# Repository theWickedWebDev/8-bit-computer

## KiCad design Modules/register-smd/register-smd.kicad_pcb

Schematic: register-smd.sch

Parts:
C1, C2, C3: C; C_0805_2012Metric; JLC C15525
C4: CP1; CP_Radial_D5.0mm_P2.50mm
D1, D2, D3, D4, D5, D6, D7, D8, D9, D10, D11, D12, D13, D14, D15, D16, D17, D18, D19, D20, D21, D22, D23, D24, D25, D26, D27, D28, D29, D30, D31, D32: LED; LED_0805_2012Metric
J1: Screw_Terminal_01x02; TerminalBlock_Phoenix_MKDS-1,5-2_1x02_P5.00mm_Horizontal
J2: Conn_01x16; PinHeader_1x16_P2.54mm_Horizontal
J8: Conn_01x18; PinHeader_1x18_P2.54mm_Horizontal
R1, R2, R3, R4, R5, R6, R7, R8, R9, R10, R11, R12, R13, R14, R15, R16, R17, R18, R19, R20, R21, R22, R23, R24, R25, R26, R27, R28, R29, R30, R31, R32, R33, R34, R35, R36, R37, R38: R_Small_US; R_0805_2012Metric; JLC C4109
U1, U3, U6: 74HC273; DIP-20_W7.62mm_Socket; JLCPCB Part # C9030
U2: 74HC08; DIP-14_W7.62mm_Socket
U4: 74LS04; DIP-14_W7.62mm_Socket
U5, U7, U47: 74HC245; DIP-20_W7.62mm_Socket

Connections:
!AI: J8.13, R32.2, U4.1
!AO: J8.14, R33.2, U4.3
!BI: J8.15, R34.2, U4.5
!BO: J8.16, R35.2, U4.9
!CI: J8.17, R36.2, U4.11
!CO: J8.18, R37.2, U4.13
/A0: D1.2 (A), J2.1, U1.2 (Q0), U47.2 (A0)
/A1: D2.2 (A), J2.2, U1.5 (Q1), U47.3 (A1)
/A2: D3.2 (A), J2.3, U1.6 (Q2), U47.4 (A2)
/A3: D4.2 (A), J2.4, U1.9 (Q3), U47.5 (A3)
/A4: D5.2 (A), J2.5, U1.12 (Q4), U47.6 (A4)
/A5: D6.2 (A), J2.6, U1.15 (Q5), U47.7 (A5)
/A6: D7.2 (A), J2.7, U1.16 (Q6), U47.8 (A6)
/A7: D8.2 (A), J2.8, U1.19 (Q7), U47.9 (A7)
/B0: D12.2 (A), J2.9, U3.2 (Q0), U5.2 (A0)
/B1: D13.2 (A), J2.10, U3.5 (Q1), U5.3 (A1)
/B2: D14.2 (A), J2.11, U3.6 (Q2), U5.4 (A2)
/B3: D15.2 (A), J2.12, U3.9 (Q3), U5.5 (A3)
/B4: D16.2 (A), J2.13, U3.12 (Q4), U5.6 (A4)
/B5: D17.2 (A), J2.14, U3.15 (Q5), U5.7 (A5)
/B6: D18.2 (A), J2.15, U3.16 (Q6), U5.8 (A6)
/B7: D19.2 (A), J2.16, U3.19 (Q7), U5.9 (A7)
/C0: D22.2 (A), U6.2 (Q0), U7.2 (A0)
/C1: D23.2 (A), U6.5 (Q1), U7.3 (A1)
/C2: D24.2 (A), U6.6 (Q2), U7.4 (A2)
/C3: D25.2 (A), U6.9 (Q3), U7.5 (A3)
/C4: D26.2 (A), U6.12 (Q4), U7.6 (A4)
/C5: D27.2 (A), U6.15 (Q5), U7.7 (A5)
/C6: D28.2 (A), U6.16 (Q6), U7.8 (A6)
/C7: D29.2 (A), U6.19 (Q7), U7.9 (A7)
AI: D9.2 (A), U2.1, U4.2
AO: D11.2 (A), U4.4, U47.19 (CE)
BI: D20.2 (A), U2.4, U4.6
BO: D21.2 (A), U4.8, U5.19 (CE)
BUS_00: J8.3, U1.3 (D0), U3.3 (D0), U5.18 (B0), U6.3 (D0), U7.18 (B0), U47.18 (B0)
BUS_01: J8.4, U1.4 (D1), U3.4 (D1), U5.17 (B1), U6.4 (D1), U7.17 (B1), U47.17 (B1)
BUS_02: J8.5, U1.7 (D2), U3.7 (D2), U5.16 (B2), U6.7 (D2), U7.16 (B2), U47.16 (B2)
BUS_03: J8.6, U1.8 (D3), U3.8 (D3), U5.15 (B3), U6.8 (D3), U7.15 (B3), U47.15 (B3)
BUS_04: J8.7, U1.13 (D4), U3.13 (D4), U5.14 (B4), U6.13 (D4), U7.14 (B4), U47.14 (B4)
BUS_05: J8.8, U1.14 (D5), U3.14 (D5), U5.13 (B5), U6.14 (D5), U7.13 (B5), U47.13 (B5)
BUS_06: J8.9, U1.17 (D6), U3.17 (D6), U5.12 (B6), U6.17 (D6), U7.12 (B6), U47.12 (B6)
BUS_07: J8.10, U1.18 (D7), U3.18 (D7), U5.11 (B7), U6.18 (D7), U7.11 (B7), U47.11 (B7)
CI: D30.2 (A), U2.9, U4.10
CLOCK: J8.11, U2.2, U2.5, U2.10
CO: D31.2 (A), U4.12, U7.19 (CE)
GND: C1.2, C2.2, C3.2, C4.2, J1.1, J8.2, R1.2, R2.2, R3.2, R4.2, R5.2, R6.2, R7.2, R8.2, R9.2, R10.2, R11.2, R12.2, R13.2, R14.2, R15.2, R16.2, R17.2, R18.2, R19.2, R20.2, R21.2, R22.2, R23.2, R24.2, R25.2, R26.2, R27.2, R28.2, R29.2, R30.2, R31.2, R32.1, R33.1, R34.1, R35.1, R36.1, R37.1, R38.2, U1.10 (GND), U2.7 (GND), U3.10 (GND), U4.7, U5.1 (A->B), U5.10 (GND), U6.10 (GND), U7.1 (A->B), U7.10 (GND), U47.1 (A->B), U47.10 (GND)
MR: D10.2 (A), J8.12, U1.1 (~Mr), U3.1 (~Mr), U6.1 (~Mr)
unnamed: D1.1 (K), R1.1
unnamed: D2.1 (K), R2.1
unnamed: D3.1 (K), R3.1
unnamed: D4.1 (K), R4.1
unnamed: D5.1 (K), R5.1
unnamed: D6.1 (K), R6.1
unnamed: D7.1 (K), R7.1
unnamed: D8.1 (K), R8.1
unnamed: D9.1 (K), R9.1
unnamed: D10.1 (K), R10.1
unnamed: D11.1 (K), R11.1
unnamed: D12.1 (K), R12.1
unnamed: D13.1 (K), R13.1
unnamed: D14.1 (K), R14.1
unnamed: D15.1 (K), R15.1
unnamed: D16.1 (K), R16.1
unnamed: D17.1 (K), R17.1
unnamed: D18.1 (K), R18.1
unnamed: D19.1 (K), R19.1
unnamed: D20.1 (K), R20.1
unnamed: D21.1 (K), R21.1
unnamed: D22.1 (K), R22.1
unnamed: D23.1 (K), R23.1
unnamed: D24.1 (K), R24.1
unnamed: D25.1 (K), R25.1
unnamed: D26.1 (K), R26.1
unnamed: D27.1 (K), R27.1
unnamed: D28.1 (K), R28.1
unnamed: D29.1 (K), R29.1
unnamed: D30.1 (K), R30.1
unnamed: D31.1 (K), R31.1
unnamed: D32.1 (K), R38.1
unnamed: U1.11 (Cp), U2.3
unnamed: U2.6, U3.11 (Cp)
unnamed: U2.8, U6.11 (Cp)
VCC: C1.1, C2.1, C3.1, C4.1, D32.2 (A), J1.2, J8.1, U1.20 (VCC), U2.14 (VCC), U3.20 (VCC), U4.14, U5.20 (VCC), U6.20 (VCC), U7.20 (VCC), U47.20 (VCC)

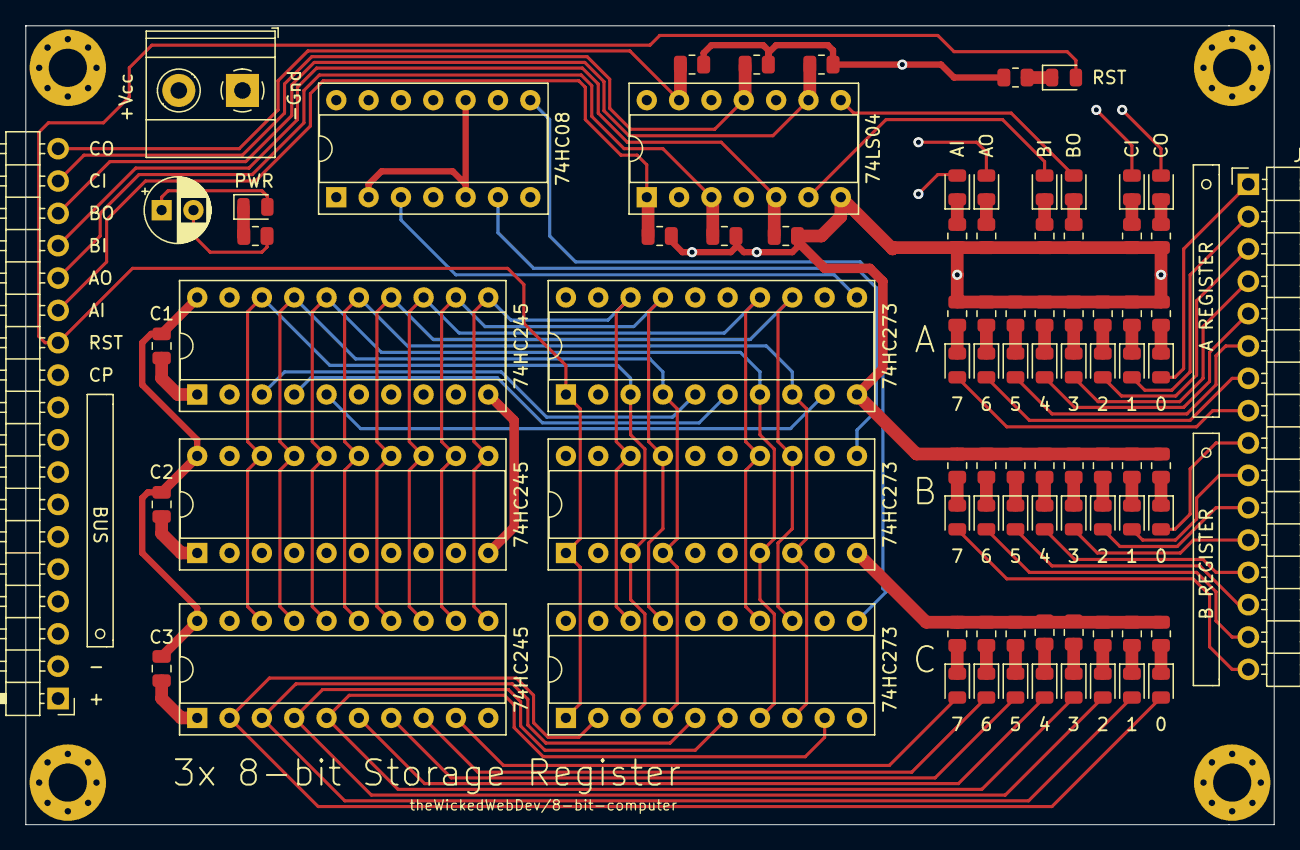
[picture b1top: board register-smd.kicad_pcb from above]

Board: 4 copper layers, 98.0 x 62.7 mm, 85 parts (0 on the bottom side), 83 nets.

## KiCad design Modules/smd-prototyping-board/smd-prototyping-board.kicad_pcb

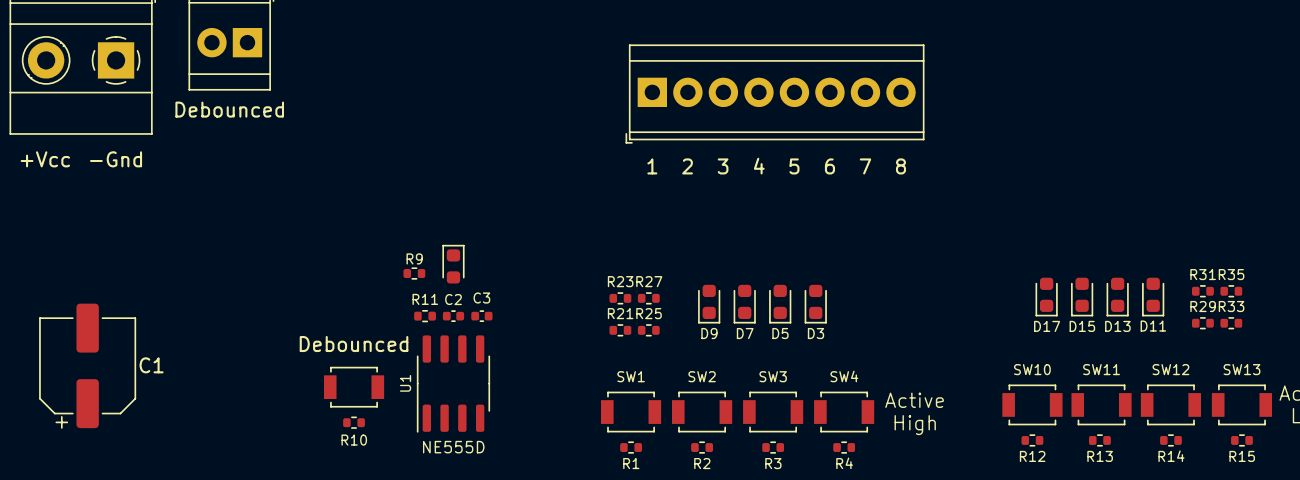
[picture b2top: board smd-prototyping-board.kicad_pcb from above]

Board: 2 copper layers, 44 parts (0 on the bottom side), 24 nets, no tracks yet.

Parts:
C1: 100uF; CP_Elec_6.3x7.7
C2: 1uF; C_0402_1005Metric
C3: 100nf; C_0402_1005Metric
D1, D3, D5, D7, D9, D11, D13, D15, D17: RED_LED; LED_0603_1608Metric
J1: Power In; TerminalBlock_Phoenix_MKDS-1,5-2_1x02_P5.00mm_Horizontal
J2: Screw_Terminal_01x08; TerminalBlock_TE_282834-8_1x08_P2.54mm_Horizontal
J4: Screw_Terminal_01x02; TerminalBlock_TE_282834-2_1x02_P2.54mm_Horizontal
R1, R2, R3, R4, R12, R13, R14, R15: 200Ω; R_0402_1005Metric
R9, R21, R23, R25, R27, R29, R31, R33, R35: 2KΩ; R_0402_1005Metric
R10: 100kΩ; R_0402_1005Metric
R11: 200kΩ; R_0402_1005Metric
SW1, SW2, SW3, SW4, SW9, SW10, SW11, SW12, SW13: SW_Push; SW_SPST_B3U-1000P
U1: NE555D; SOIC-8_3.9x4.9mm_P1.27mm

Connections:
ACTIVE_HIGH_BTN_01: D9.2, J2.1, R1.2, SW1.1
ACTIVE_HIGH_BTN_02: D7.2, J2.2, R2.2, SW2.1
ACTIVE_HIGH_BTN_03: D5.2, J2.3, R3.2, SW3.1
ACTIVE_HIGH_BTN_04: D3.2, J2.4, R4.2, SW4.1
ACTIVE_LOW_BTN_01: D17.2, J2.5, R12.2, SW10.1
ACTIVE_LOW_BTN_02: D15.2, J2.6, R13.2, SW11.1
ACTIVE_LOW_BTN_03: D13.2, J2.7, R14.2, SW12.1
ACTIVE_LOW_BTN_04: D11.2, J2.8, R15.2, SW13.1
GND: C1.2, C2.1, C3.2, J1.1, R9.1, R21.1, R23.1, R25.1, R27.1, R29.1, R31.1, R33.1, R35.1, SW9.1, SW10.2, SW11.2, SW12.2, SW13.2, U1.1
unnamed: C2.2, R11.1, U1.6, U1.7
unnamed: C3.1, U1.5
unnamed: D1.1, R9.2
unnamed: D1.2, J4.1, J4.2, U1.3
unnamed: D3.1, R21.2
unnamed: D5.1, R23.2
unnamed: D7.1, R25.2
unnamed: D9.1, R27.2
unnamed: D11.1, R29.2
unnamed: D13.1, R31.2
unnamed: D15.1, R33.2
unnamed: D17.1, R35.2
unnamed: R1.1, R2.1, R3.1, R4.1
unnamed: R10.1, SW9.2, U1.2
VCC: C1.1, J1.2, R10.2, R11.2, R12.1, R13.1, R14.1, R15.1, SW1.2, SW2.2, SW3.2, SW4.2, U1.4, U1.8

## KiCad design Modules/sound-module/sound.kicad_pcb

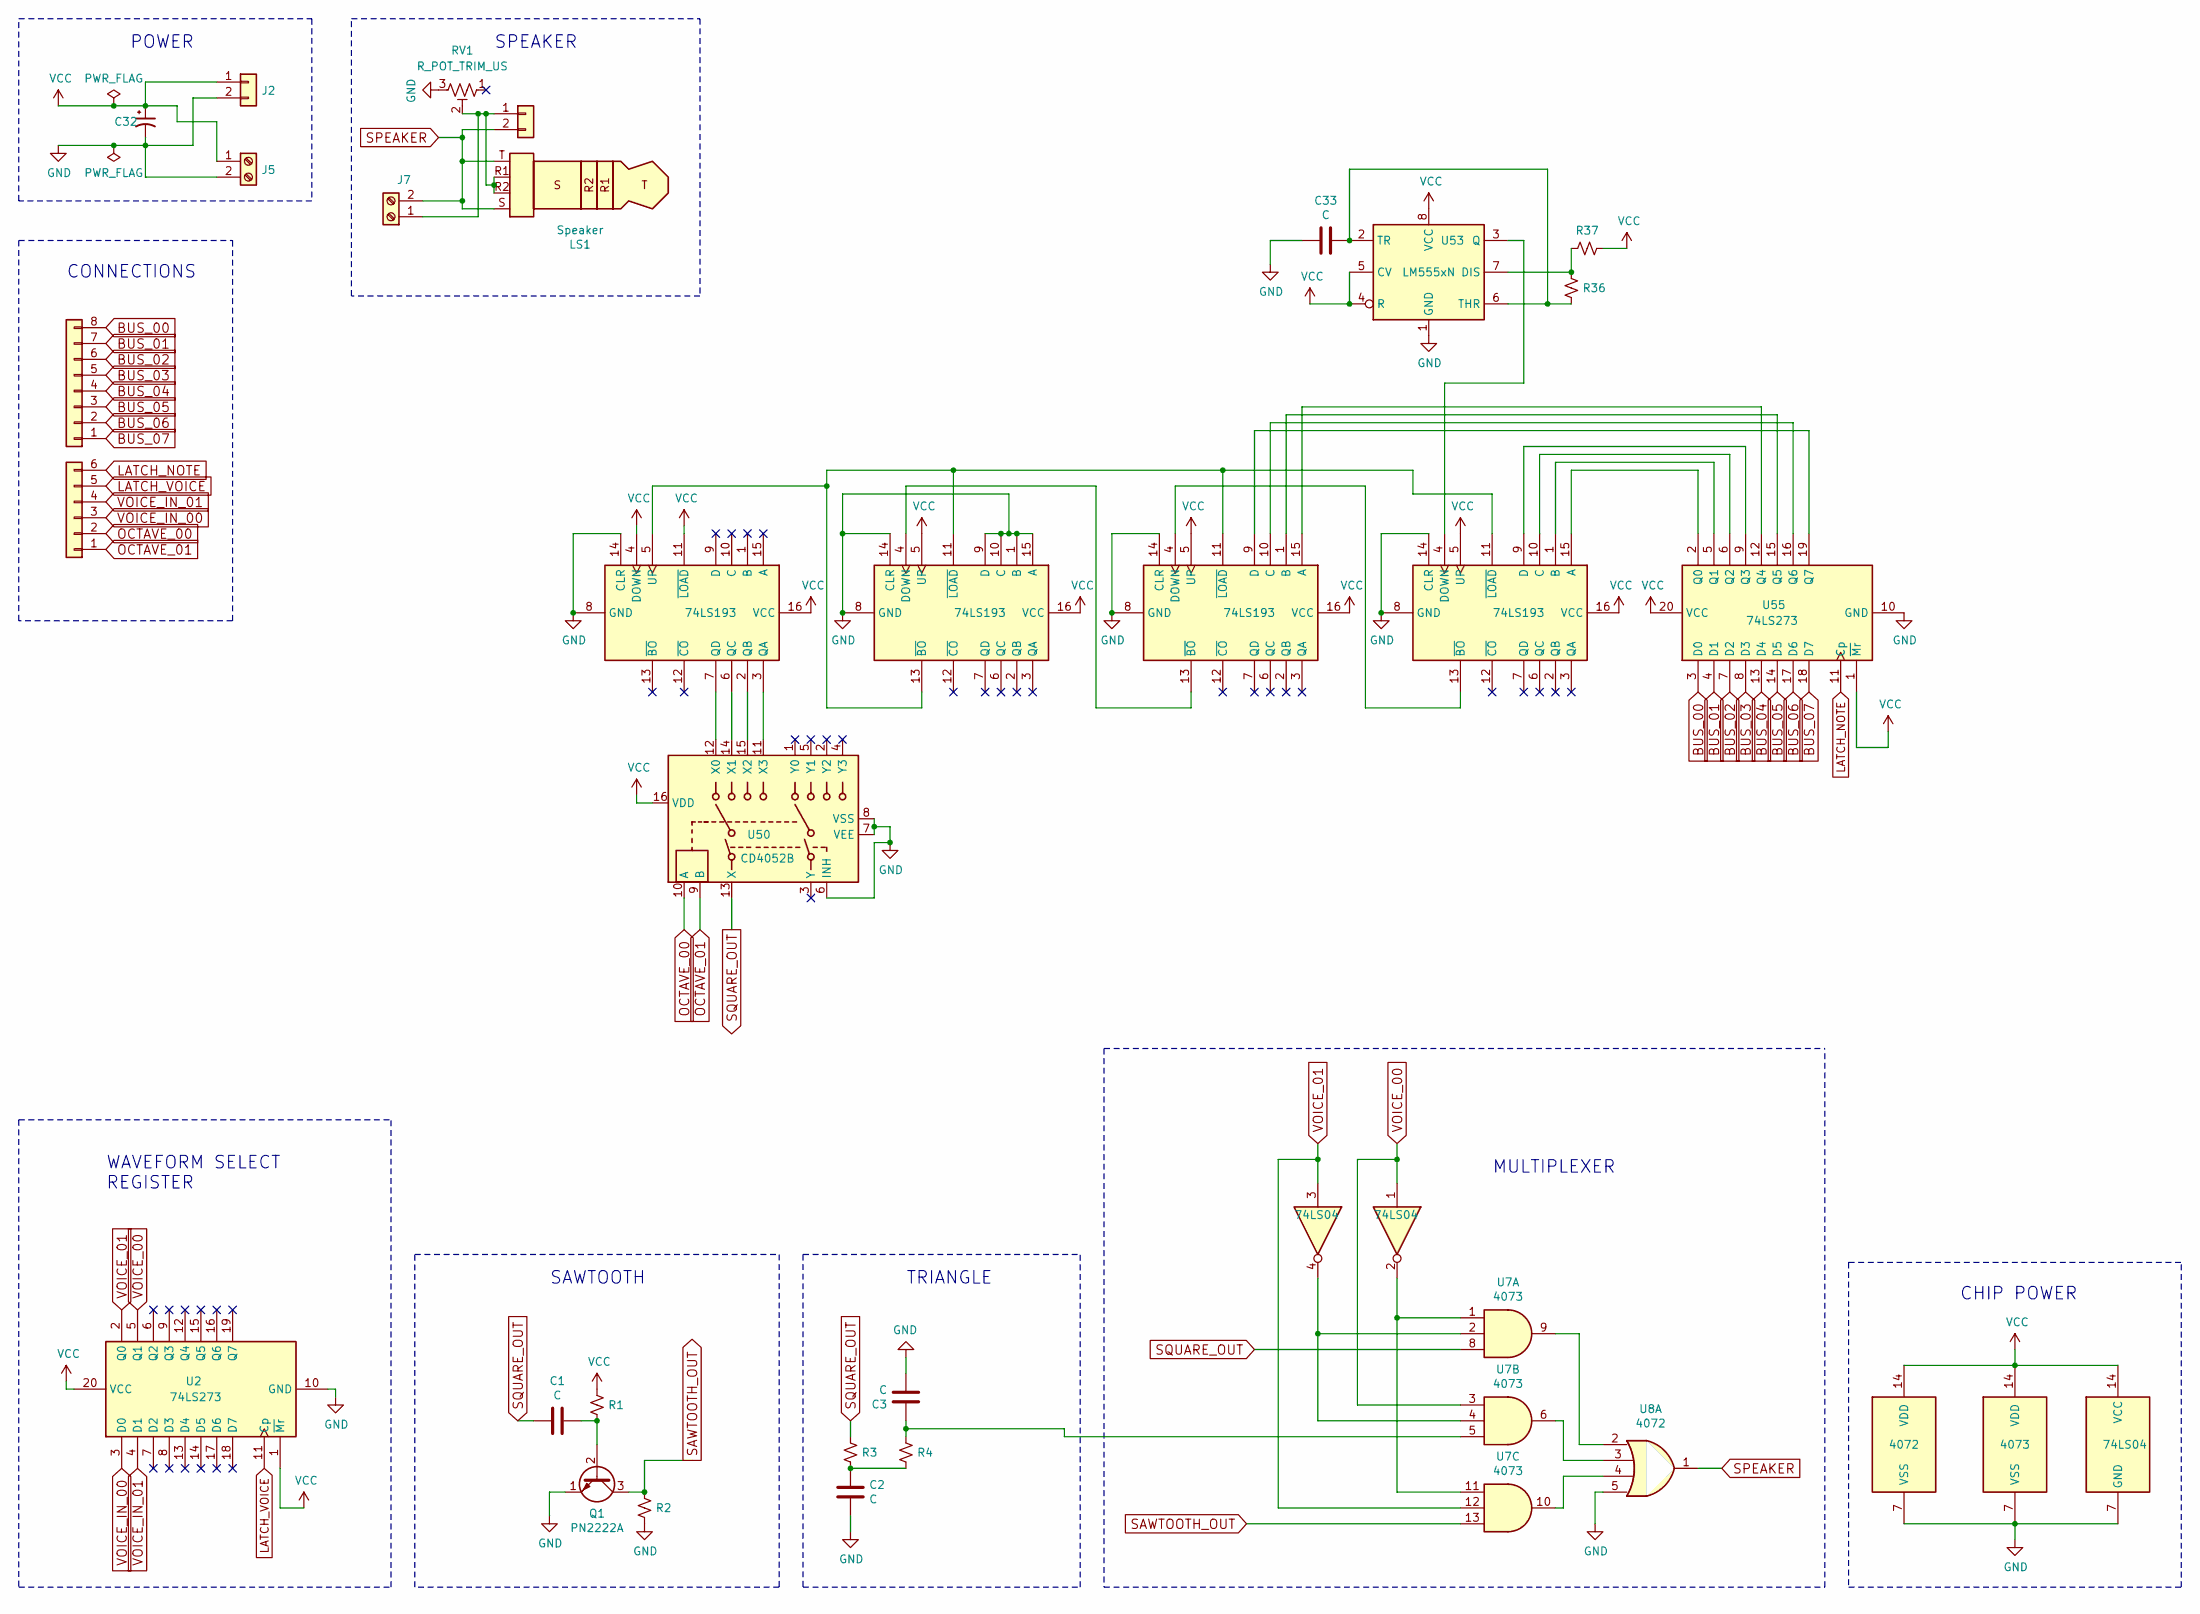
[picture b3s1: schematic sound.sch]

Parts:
C1, C2, C3: C; C_Disc_D4.7mm_W2.5mm_P5.00mm
C32: CP1_Small; CP_Radial_D5.0mm_P2.50mm
C33: C; C_Disc_D3.8mm_W2.6mm_P2.50mm
J2, J73: Conn_01x02; PinHeader_1x02_P2.54mm_Vertical
J5, J7: Screw_Terminal_01x02; TerminalBlock_Phoenix_MKDS-1,5-2_1x02_P5.00mm_Horizontal
J68: Conn_01x08; PinHeader_1x08_P2.54mm_Vertical
J69: Conn_01x06; PinHeader_1x06_P2.54mm_Vertical
LS1: Speaker; 3.5mm_Audio_Jack_PJ31640M
Q1: PN2222A; TO-92_Inline
R1, R2, R3, R4, R36, R37: R_Small_US; R_Axial_DIN0207_L6.3mm_D2.5mm_P10.16mm_Horizontal
RV1: R_POT_TRIM_US; Potentiometer_Bourns_3386F_Vertical
U1, U3, U4, U5: 74LS193; DIP-16_W7.62mm
U2, U55: 74LS273; DIP-20_W7.62mm
U6: 74LS04; DIP-14_W7.62mm
U7: 4073; DIP-14_W7.62mm
U8: 4072; DIP-16_W7.62mm
U50: CD4052B; DIP-16_W7.62mm
U53: LM555xN; DIP-8_W7.62mm

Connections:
BUS_00: J68.8, U55.3 (D0)
BUS_01: J68.7, U55.4 (D1)
BUS_02: J68.6, U55.7 (D2)
BUS_03: J68.5, U55.8 (D3)
BUS_04: J68.4, U55.13 (D4)
BUS_05: J68.3, U55.14 (D5)
BUS_06: J68.2, U55.17 (D6)
BUS_07: J68.1, U55.18 (D7)
GND: C2.1, C3.2, C32.2, C33.1, J2.2, J5.2, Q1.1 (E), R2.1, RV1.3, U1.8 (GND), U1.14 (CLR), U2.10 (GND), U3.1 (B), U3.8 (GND), U3.9 (D), U3.10 (C), U3.14 (CLR), U3.15 (A), U4.8 (GND), U4.14 (CLR), U5.8 (GND), U5.14 (CLR), U6.7 (GND), U7.7 (VSS), U8.5, U8.7 (VSS), U50.6 (INH), U50.7 (VEE), U50.8 (VSS), U53.1 (GND), U55.10 (GND)
LATCH_NOTE: J69.6, U55.11 (Cp)
LATCH_VOICE: J69.5, U2.11 (Cp)
unnamed: C1.1, Q1.2 (B), R1.1
unnamed: C2.2, R3.1, R4.1
unnamed: C3.1, R4.2, U7.5
unnamed: C33.2, R36.1, U53.2 (TR), U53.6 (THR)
unnamed: J7.1, J73.1, LS1.R1, LS1.R2, RV1.2
unnamed: R36.2, R37.2, U53.7 (DIS)
unnamed: U1.2 (QB), U50.15 (X2)
unnamed: U1.3 (QA), U50.11 (X3)
unnamed: U1.5 (UP), U3.11 (~LOAD), U3.13 (~BO), U4.11 (~LOAD), U5.11 (~LOAD)
unnamed: U1.6 (QC), U50.14 (X1)
unnamed: U1.7 (QD), U50.12 (X0)
unnamed: U3.4 (DOWN), U4.13 (~BO)
unnamed: U4.1 (B), U55.15 (Q5)
unnamed: U4.4 (DOWN), U5.13 (~BO)
unnamed: U4.9 (D), U55.19 (Q7)
unnamed: U4.10 (C), U55.16 (Q6)
unnamed: U4.15 (A), U55.12 (Q4)
unnamed: U5.1 (B), U55.5 (Q1)
unnamed: U5.4 (DOWN), U53.3 (Q)
unnamed: U5.9 (D), U55.9 (Q3)
unnamed: U5.10 (C), U55.6 (Q2)
unnamed: U5.15 (A), U55.2 (Q0)
unnamed: U6.2, U7.1, U7.11
unnamed: U6.4, U7.2, U7.4
unnamed: U7.6, U8.3
unnamed: U7.9, U8.2
unnamed: U7.10, U8.4
OCTAVE_00: J69.2, U50.10 (A)
OCTAVE_01: J69.1, U50.9 (B)
SAWTOOTH_OUT: Q1.3 (C), R2.2, U7.13
SPEAKER: J7.2, J73.2, LS1.S, LS1.T, U8.1
SQUARE_OUT: C1.2, R3.2, U7.8, U50.13 (X)
VCC: C32.1, J2.1, J5.1, R1.2, R37.1, U1.4 (DOWN), U1.11 (~LOAD), U1.16 (VCC), U2.1 (~Mr), U2.20 (VCC), U3.5 (UP), U3.16 (VCC), U4.5 (UP), U4.16 (VCC), U5.5 (UP), U5.16 (VCC), U6.14 (VCC), U7.14 (VDD), U8.14 (VDD), U50.16 (VDD), U53.4 (R), U53.5 (CV), U53.8 (VCC), U55.1 (~Mr), U55.20 (VCC)
VOICE_00: U2.5 (Q1), U6.1, U7.3
VOICE_01: U2.2 (Q0), U6.3, U7.12
VOICE_IN_00: J69.3, U2.3 (D0)
VOICE_IN_01: J69.4, U2.4 (D1)

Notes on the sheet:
POWER
SPEAKER
CONNECTIONS
SAWTOOTH
TRIANGLE
MULTIPLEXER
WAVEFORM SELECT REGISTER
CHIP POWER

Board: 4 copper layers, 31 parts (0 on the bottom side), 48 nets, no tracks yet.

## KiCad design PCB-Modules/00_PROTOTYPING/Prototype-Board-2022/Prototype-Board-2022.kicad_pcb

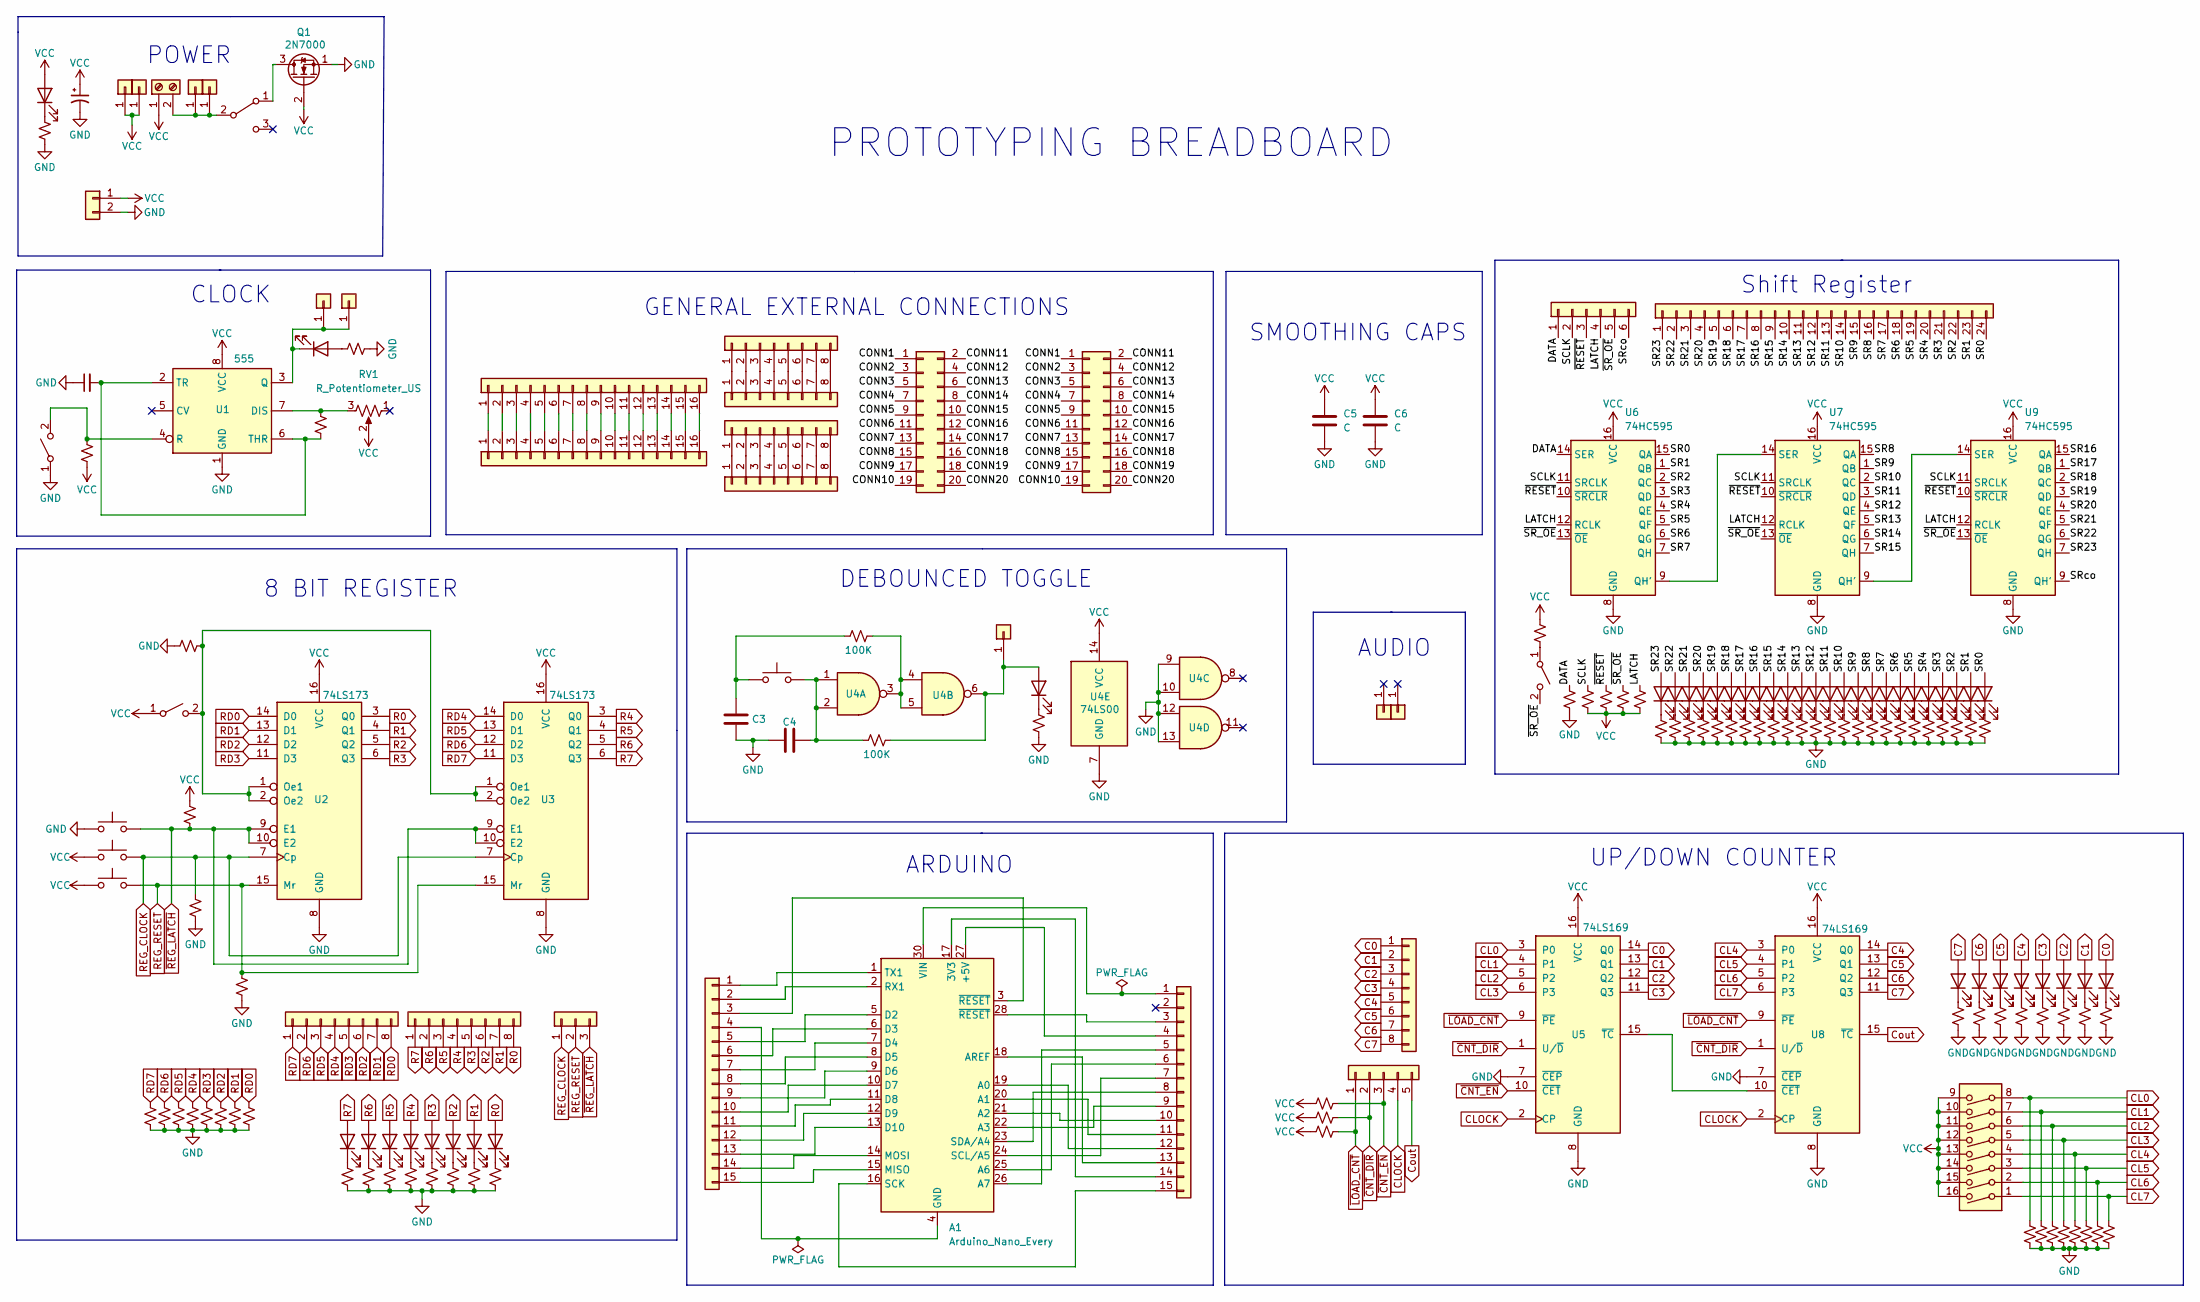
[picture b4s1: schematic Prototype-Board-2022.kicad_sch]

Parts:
A1: Arduino_Nano_Every; Arduino_Nano
C1: C_Polarized_Small_US; CP_Elec_4x5.3
C2: C_Small; C_0805_2012Metric
C3, C4, C5, C6: C; C_0805_2012Metric
D1, D2: LED; LED_1206_3216Metric
D3, D4, D5, D6, D7, D8, D9, D10, D11, D12, D13, D14, D15, D16, D17, D18, D19, D20, D21, D22, D23, D24, D25, D26, D27, D28, D29, D30, D31, D32, D33, D34, D35, D36, D37, D38, D39, D40, D41, D42, D43: LED; LED_0805_2012Metric
J1: Conn_01x02; TerminalBlock_TE_282834-2_1x02_P2.54mm_Horizontal
J2, J3, J5, J6, J8, J10, J21, J24, J26: Conn_01x01; Banana_Jack_1Pin_2mm
J4: Screw_Terminal_01x02; TerminalBlock_Phoenix_MKDS-1,5-2_1x02_P5.00mm_Horizontal
J9, J11, J16, J18, J27: Conn_01x08; PinHeader_1x08_P2.54mm_Vertical
J12: Conn_01x03; PinHeader_1x03_P2.54mm_Vertical
J13: Conn_01x16; PinHeader_1x16_P2.54mm_Horizontal
J14: Conn_01x16; PinSocket_1x16_P2.54mm_Vertical
J15, J23: Conn_01x15; PinHeader_1x15_P2.54mm_Vertical
J17, J19: Conn_01x08; PinHeader_1x08_P2.54mm_Horizontal
J20: Conn_02x20_Odd_Even; IDC-Header_2x10_P2.54mm_Vertical
J22: Conn_02x10_Odd_Even; PinHeader_2x10_P2.54mm_Vertical
J25: Conn_01x05; PinHeader_1x05_P2.54mm_Vertical
J28: Conn_01x06; PinHeader_1x06_P2.54mm_Vertical
J29: Conn_01x24; PinHeader_1x24_P2.54mm_Vertical
Q1: 2N7000; TO-92_Inline
R1, R2, R3, R4, R5, R6, R7, R8, R9, R10, R11, R12, R13, R14, R15, R16, R17, R18, R19, R20, R21, R22, R23, R24, R25, R26, R27, R28, R29, R30, R31, R32, R33, R34, R35, R36, R37, R38, R39, R40, R41, R42, R43, R44, R45, R46, R47, R48, R49, R50, R51, R52, R53, R54, R55, R56, R57, R58, R59, R60, R61, R62, R63, R64, R65, R66, R67, R68, R69, R70, R71, R72, R73, R74, R75, R76: R_Small_US; R_0805_2012Metric
RV1: R_Potentiometer_US; potentiometer-trim-pot
SW1, SW5, SW8: SW_SPST; spdt-slide-switch
SW2, SW3, SW4, SW7: SW_Push; SW_PUSH_6mm
SW6: SW_DPDT_x2; THT-DPDT
SW9: SW_DIP_x08; SW_DIP_SPSTx08_Slide_9.78x22.5mm_W7.62mm_P2.54mm
U1: 555; SOIC-8_3.9x4.9mm_P1.27mm
U2, U3: 74LS173; SOIC-16_3.9x9.9mm_P1.27mm
U4: 74LS00
U5, U8: 74LS169; SOIC-16_3.9x9.9mm_P1.27mm
U6, U7, U9: 74HC595; SOIC-16_3.9x9.9mm_P1.27mm

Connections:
/CONN1: J20.1, J22.1
/CONN2: J20.3, J22.3
/CONN3: J20.5, J22.5
/CONN4: J20.7, J22.7
/CONN5: J20.9, J22.9
/CONN6: J20.11, J22.11
/CONN7: J20.13, J22.13
/CONN8: J20.15, J22.15
/CONN9: J20.17, J22.17
/CONN10: J20.19, J22.19
/CONN11: J20.2, J22.2
/CONN12: J20.4, J22.4
/CONN13: J20.6, J22.6
/CONN14: J20.8, J22.8
/CONN15: J20.10, J22.10
/CONN16: J20.12, J22.12
/CONN17: J20.14, J22.14
/CONN18: J20.16, J22.16
/CONN19: J20.18, J22.18
/CONN20: J20.20, J22.20
/DATA: J28.1, R32.1, U6.14 (SER)
/LATCH: J28.4, R36.1, U6.12 (RCLK), U7.12 (RCLK), U9.12 (RCLK)
/SCLK: J28.2, R33.1, U6.11 (SRCLK), U7.11 (SRCLK), U9.11 (SRCLK)
/SR0: D37.2 (A), J29.24, U6.15 (QA)
/SR1: D35.2 (A), J29.23, U6.1 (QB)
/SR2: D33.2 (A), J29.22, U6.2 (QC)
/SR3: D32.2 (A), J29.21, U6.3 (QD)
/SR4: D31.2 (A), J29.20, U6.4 (QE)
/SR5: D30.2 (A), J29.19, U6.5 (QF)
/SR6: D29.2 (A), J29.18, U6.6 (QG)
/SR7: D28.2 (A), J29.17, U6.7 (QH)
/SR8: D27.2 (A), J29.16, U7.15 (QA)
/SR9: D26.2 (A), J29.15, U7.1 (QB)
/SR10: D25.2 (A), J29.14, U7.2 (QC)
/SR11: D24.2 (A), J29.13, U7.3 (QD)
/SR12: D23.2 (A), J29.12, U7.4 (QE)
/SR13: D22.2 (A), J29.11, U7.5 (QF)
/SR14: D21.2 (A), J29.10, U7.6 (QG)
/SR15: D20.2 (A), J29.9, U7.7 (QH)
/SR16: D19.2 (A), J29.8, U9.15 (QA)
/SR17: D18.2 (A), J29.7, U9.1 (QB)
/SR18: D17.2 (A), J29.6, U9.2 (QC)
/SR19: D16.2 (A), J29.5, U9.3 (QD)
/SR20: D15.2 (A), J29.4, U9.4 (QE)
/SR21: D14.2 (A), J29.3, U9.5 (QF)
/SR22: D13.2 (A), J29.2, U9.6 (QG)
/SR23: D12.2 (A), J29.1, U9.7 (QH)
/SRco: J28.6, U9.9 (QH')
/~RESET: J28.3, R34.1, U6.10 (~SRCLR), U7.10 (~SRCLR), U9.10 (~SRCLR)
/~SR_OE: J28.5, R35.1, SW8.2 (B), U6.13 (~OE), U7.13 (~OE), U9.13 (~OE)
C0: D43.2 (A), J27.1, U5.14 (Q0)
C1: D42.2 (A), J27.2, U5.13 (Q1)
C2: D41.2 (A), J27.3, U5.12 (Q2)
C3: D40.2 (A), J27.4, U5.11 (Q3)
C4: D39.2 (A), J27.5, U8.14 (Q0)
C5: D38.2 (A), J27.6, U8.13 (Q1)
C6: D36.2 (A), J27.7, U8.12 (Q2)
C7: D34.2 (A), J27.8, U8.11 (Q3)
CL0: R65.1, SW9.8, U5.3 (P0)
CL1: R66.1, SW9.7, U5.4 (P1)
CL2: R68.1, SW9.6, U5.5 (P2)
CL3: R70.1, SW9.5, U5.6 (P3)
CL4: R71.1, SW9.4, U8.3 (P0)
CL5: R73.1, SW9.3, U8.4 (P1)
CL6: R74.1, SW9.2, U8.5 (P2)
CL7: R76.1, SW9.1, U8.6 (P3)
CLOCK: J25.4, U5.2 (CP), U8.2 (CP)
Cout: J25.5, U8.15 (~TC)
GND: C1.2, C2.1, C3.2, C4.1, C5.2, C6.2, J1.2, Q1.1 (S), R1.2, R3.2, R4.2, R5.2, R6.1, R8.2, R9.2, R10.2, R11.2, R12.2, R13.2, R14.2, R16.2, R17.2, R18.2, R19.2, R20.2, R21.2, R22.2, R23.2, R24.2, R27.2, R32.2, R37.2, R38.2, R39.2, R40.2, R41.2, R42.2, R43.2, R44.2, R45.2, R46.2, R47.2, R48.2, R49.2, R50.2, R51.2, R52.2, R53.2, R54.2, R55.2, R56.2, R57.2, R58.2, R59.2, R60.2, R61.2, R62.2, R63.2, R64.2, R65.2, R66.2, R67.2, R68.2, R69.2, R70.2, R71.2, R72.2, R73.2, R74.2, R75.2, R76.2, SW1.1 (A), SW2.1, U1.1 (GND), U2.8 (GND), U3.8 (GND), U4.7 (GND), U4.9, U4.10, U4.12, U4.13, U5.7 (~CEP), U5.8 (GND), U6.8 (GND), U7.8 (GND), U8.7 (~CEP), U8.8 (GND), U9.8 (GND)
unnamed: A1.1 (TX1), J15.1
unnamed: A1.2 (RX1), J15.2
unnamed: A1.3 (~RESET), J15.3
unnamed: A1.5 (D2), J15.5
unnamed: A1.6 (D3), J15.6
unnamed: A1.7 (D4), J15.7
unnamed: A1.8 (D5), J15.8
unnamed: A1.9 (D6), J15.9
unnamed: A1.10 (D7), J15.10
unnamed: A1.11 (D8), J15.11
unnamed: A1.12 (D9), J15.12
unnamed: A1.13 (D10), J15.13
unnamed: A1.14 (MOSI), J15.14
unnamed: A1.15 (MISO), J15.15
unnamed: A1.16 (SCK), J23.15
unnamed: A1.17 (3V3), J23.14
unnamed: A1.18 (AREF), J23.13
unnamed: A1.19 (A0), J23.12
unnamed: A1.20 (A1), J23.11
unnamed: A1.21 (A2), J23.10
unnamed: A1.22 (A3), J23.9
unnamed: A1.23 (SDA/A4), J23.8
unnamed: A1.24 (SCL/A5), J23.7
unnamed: A1.25 (A6), J23.6
unnamed: A1.26 (A7), J23.5
unnamed: A1.27 (+5V), J23.4
unnamed: A1.28 (~RESET), J23.3
unnamed: A1.4 (GND), A1.29 (GND), J15.4
unnamed: A1.30 (VIN), J23.1
unnamed: C2.2, R15.2, U1.2 (TR), U1.6 (THR)
unnamed: C3.1, R25.1, SW7.1
unnamed: C4.2, R26.1, SW7.2, U4.1, U4.2
unnamed: D1.1 (K), R1.1
unnamed: D2.1 (K), J8.1, J10.1, U1.3 (Q)
unnamed: D2.2 (A), R17.1
unnamed: D3.1 (K), R16.1
unnamed: D4.1 (K), R18.1
unnamed: D5.1 (K), R19.1
unnamed: D6.1 (K), R20.1
unnamed: D7.1 (K), R21.1
unnamed: D8.1 (K), R22.1
unnamed: D9.1 (K), R23.1
unnamed: D10.1 (K), R24.1
unnamed: D11.1 (K), R27.1
unnamed: D11.2 (A), J21.1, R26.2, U4.6
unnamed: D12.1 (K), R37.1
unnamed: D13.1 (K), R38.1
unnamed: D14.1 (K), R39.1
unnamed: D15.1 (K), R40.1
unnamed: D16.1 (K), R41.1
unnamed: D17.1 (K), R42.1
unnamed: D18.1 (K), R43.1
unnamed: D19.1 (K), R44.1
unnamed: D20.1 (K), R45.1
unnamed: D21.1 (K), R46.1
unnamed: D22.1 (K), R47.1
unnamed: D23.1 (K), R48.1
unnamed: D24.1 (K), R49.1
unnamed: D25.1 (K), R50.1
unnamed: D26.1 (K), R51.1
unnamed: D27.1 (K), R52.1
unnamed: D28.1 (K), R53.1
unnamed: D29.1 (K), R54.1
unnamed: D30.1 (K), R55.1
unnamed: D31.1 (K), R56.1
unnamed: D32.1 (K), R57.1
unnamed: D33.1 (K), R58.1
unnamed: D34.1 (K), R59.1
unnamed: D35.1 (K), R60.1
unnamed: D36.1 (K), R61.1
unnamed: D37.1 (K), R62.1
unnamed: D38.1 (K), R63.1
unnamed: D39.1 (K), R64.1
unnamed: D40.1 (K), R67.1
unnamed: D41.1 (K), R69.1
unnamed: D42.1 (K), R72.1
unnamed: D43.1 (K), R75.1
unnamed: J4.2, J5.1, J6.1, SW6.2 (B)
unnamed: J13.1, J14.1
unnamed: J13.2, J14.2
unnamed: J13.3, J14.3
unnamed: J13.4, J14.4
unnamed: J13.5, J14.5
unnamed: J13.6, J14.6
unnamed: J13.7, J14.7
unnamed: J13.8, J14.8
unnamed: J13.9, J14.9
unnamed: J13.10, J14.10
unnamed: J13.11, J14.11
unnamed: J13.12, J14.12
unnamed: J13.13, J14.13
unnamed: J13.14, J14.14
unnamed: J13.15, J14.15
unnamed: J13.16, J14.16
unnamed: J16.1, J17.1
unnamed: J16.2, J17.2
unnamed: J16.3, J17.3
unnamed: J16.4, J17.4
unnamed: J16.5, J17.5
unnamed: J16.6, J17.6
unnamed: J16.7, J17.7
unnamed: J16.8, J17.8
unnamed: J18.1, J19.1
unnamed: J18.2, J19.2
unnamed: J18.3, J19.3
unnamed: J18.4, J19.4
unnamed: J18.5, J19.5
unnamed: J18.6, J19.6
unnamed: J18.7, J19.7
unnamed: J18.8, J19.8
unnamed: Q1.3 (D), SW6.1 (A)
unnamed: R2.1, SW1.2 (B), U1.4 (R)
unnamed: R6.2, SW5.2 (B), U2.1 (Oe1), U2.2 (Oe2), U3.1 (Oe1), U3.2 (Oe2)
unnamed: R15.1, RV1.3, U1.7 (DIS)
unnamed: R25.2, U4.3, U4.4, U4.5
unnamed: R31.2, SW8.1 (A)
unnamed: U5.15 (~TC), U8.10 (~CET)
unnamed: U6.9 (QH'), U7.14 (SER)
unnamed: U7.9 (QH'), U9.14 (SER)
R0: D10.2 (A), J11.8, U2.3 (Q0)
R1: D9.2 (A), J11.7, U2.4 (Q1)
R2: D8.2 (A), J11.6, U2.5 (Q2)
R3: D7.2 (A), J11.5, U2.6 (Q3)
R4: D6.2 (A), J11.4, U3.3 (Q0)
R5: D5.2 (A), J11.3, U3.4 (Q1)
R6: D4.2 (A), J11.2, U3.5 (Q2)
R7: D3.2 (A), J11.1, U3.6 (Q3)
RD0: J9.8, R14.1, U2.14 (D0)
RD1: J9.7, R12.1, U2.13 (D1)
RD2: J9.6, R11.1, U2.12 (D2)
RD3: J9.5, R10.1, U2.11 (D3)
RD4: J9.4, R8.1, U3.14 (D0)
RD5: J9.3, R5.1, U3.13 (D1)
RD6: J9.2, R4.1, U3.12 (D2)
RD7: J9.1, R3.1, U3.11 (D3)
REG_CLOCK: J12.1, R9.1, SW3.2, U2.7 (Cp), U3.7 (Cp)
REG_RESET: J12.2, R13.1, SW4.2, U2.15 (Mr), U3.15 (Mr)
VCC: C1.1, C5.1, C6.1, D1.2 (A), J1.1, J2.1, J3.1, J4.1, Q1.2 (G), R2.2, R7.2, R28.2, R29.2, R30.2, R31.1, R33.2, R34.2, R35.2, R36.2, RV1.2, SW3.1, SW4.1, SW5.1 (A), SW9.9, SW9.10, SW9.11, SW9.12, SW9.13, SW9.14, SW9.15, SW9.16, U1.8 (VCC), U2.16 (VCC), U3.16 (VCC), U4.14 (VCC), U5.16 (VCC), U6.16 (VCC), U7.16 (VCC), U8.16 (VCC), U9.16 (VCC)
~CNT_DIR: J25.2, R29.1, U5.1 (U/~D), U8.1 (U/~D)
~CNT_EN: J25.3, R28.1, U5.10 (~CET)
~LOAD_CNT: J25.1, R30.1, U5.9 (~PE), U8.9 (~PE)
~REG_LATCH: J12.3, R7.1, SW2.2, U2.9 (E1), U2.10 (E2), U3.9 (E1), U3.10 (E2)

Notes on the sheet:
CLOCK
Shift Register
GENERAL EXTERNAL CONNECTIONS
PROTOTYPING BREADBOARD
DEBOUNCED TOGGLE
ARDUINO
UP/DOWN COUNTER
AUDIO
SMOOTHING CAPS
POWER
8 BIT REGISTER

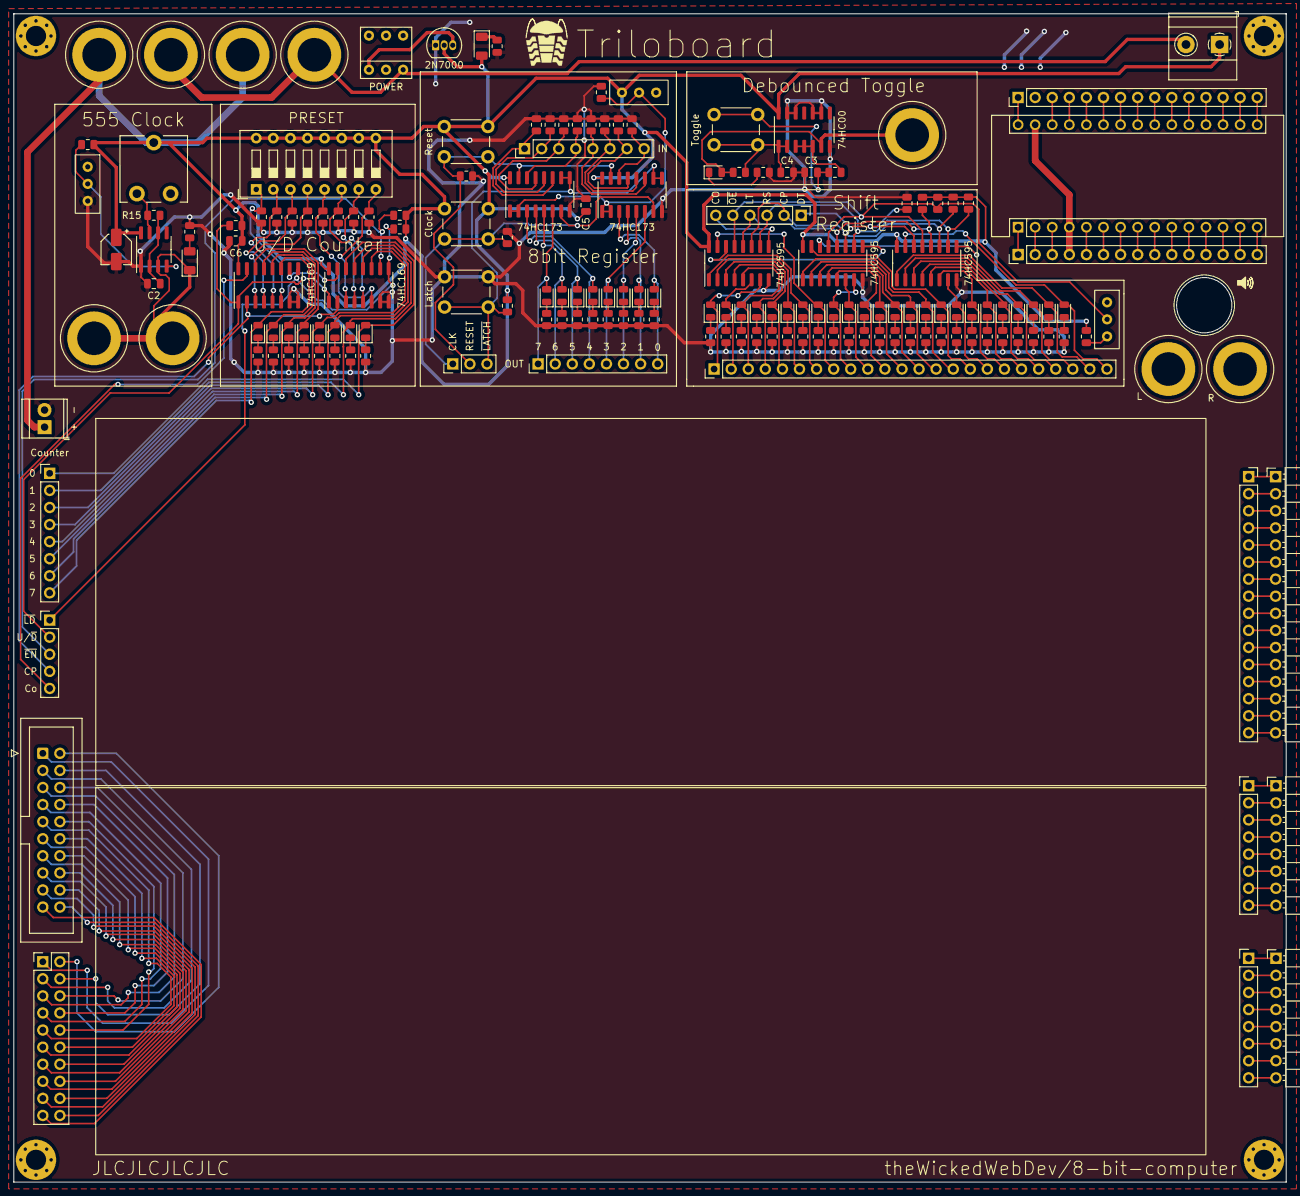
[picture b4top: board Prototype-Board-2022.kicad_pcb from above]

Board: 2 copper layers, 189.2 x 173.7 mm, 174 parts (0 on the bottom side), 211 nets.
